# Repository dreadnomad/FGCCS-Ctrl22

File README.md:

# FGCCS-Ctrl22
Atmega4808-based charge controller for electric vehicles.
Inspired by SmartEVSE.

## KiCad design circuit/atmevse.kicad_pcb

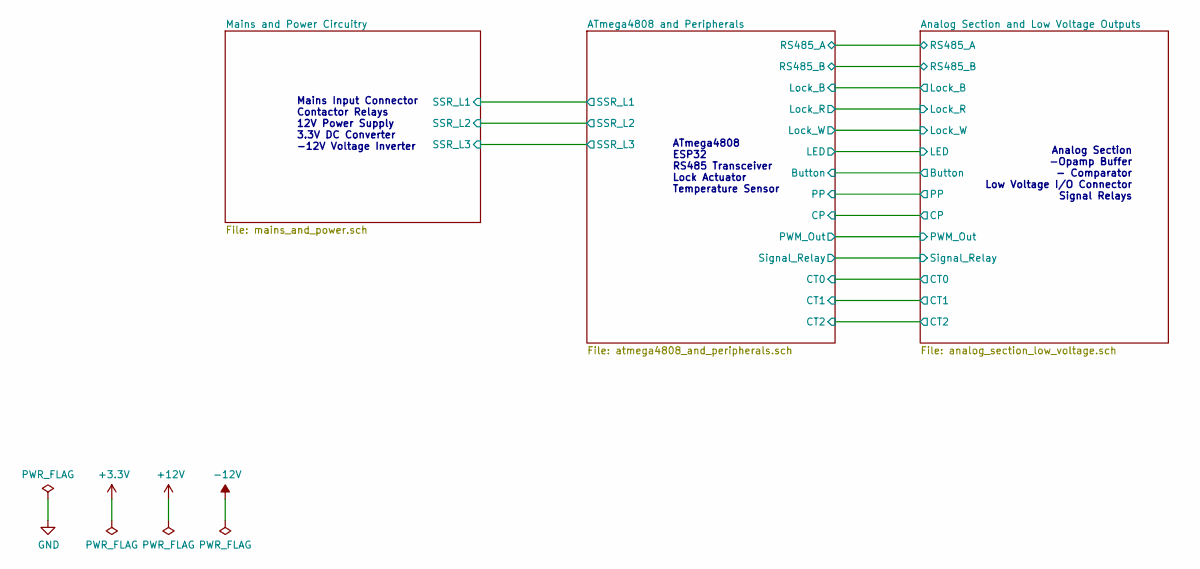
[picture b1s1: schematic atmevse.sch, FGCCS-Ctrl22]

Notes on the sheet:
Mains Input Connector Contactor Relays 12V Power Supply 3.3V DC Converter -12V Voltage Inverter
ATmega4808 ESP32 RS485 Transceiver Lock Actuator Temperature Sensor
Analog Section -Opamp Buffer - Comparator Low Voltage I/O Connector Signal Relays

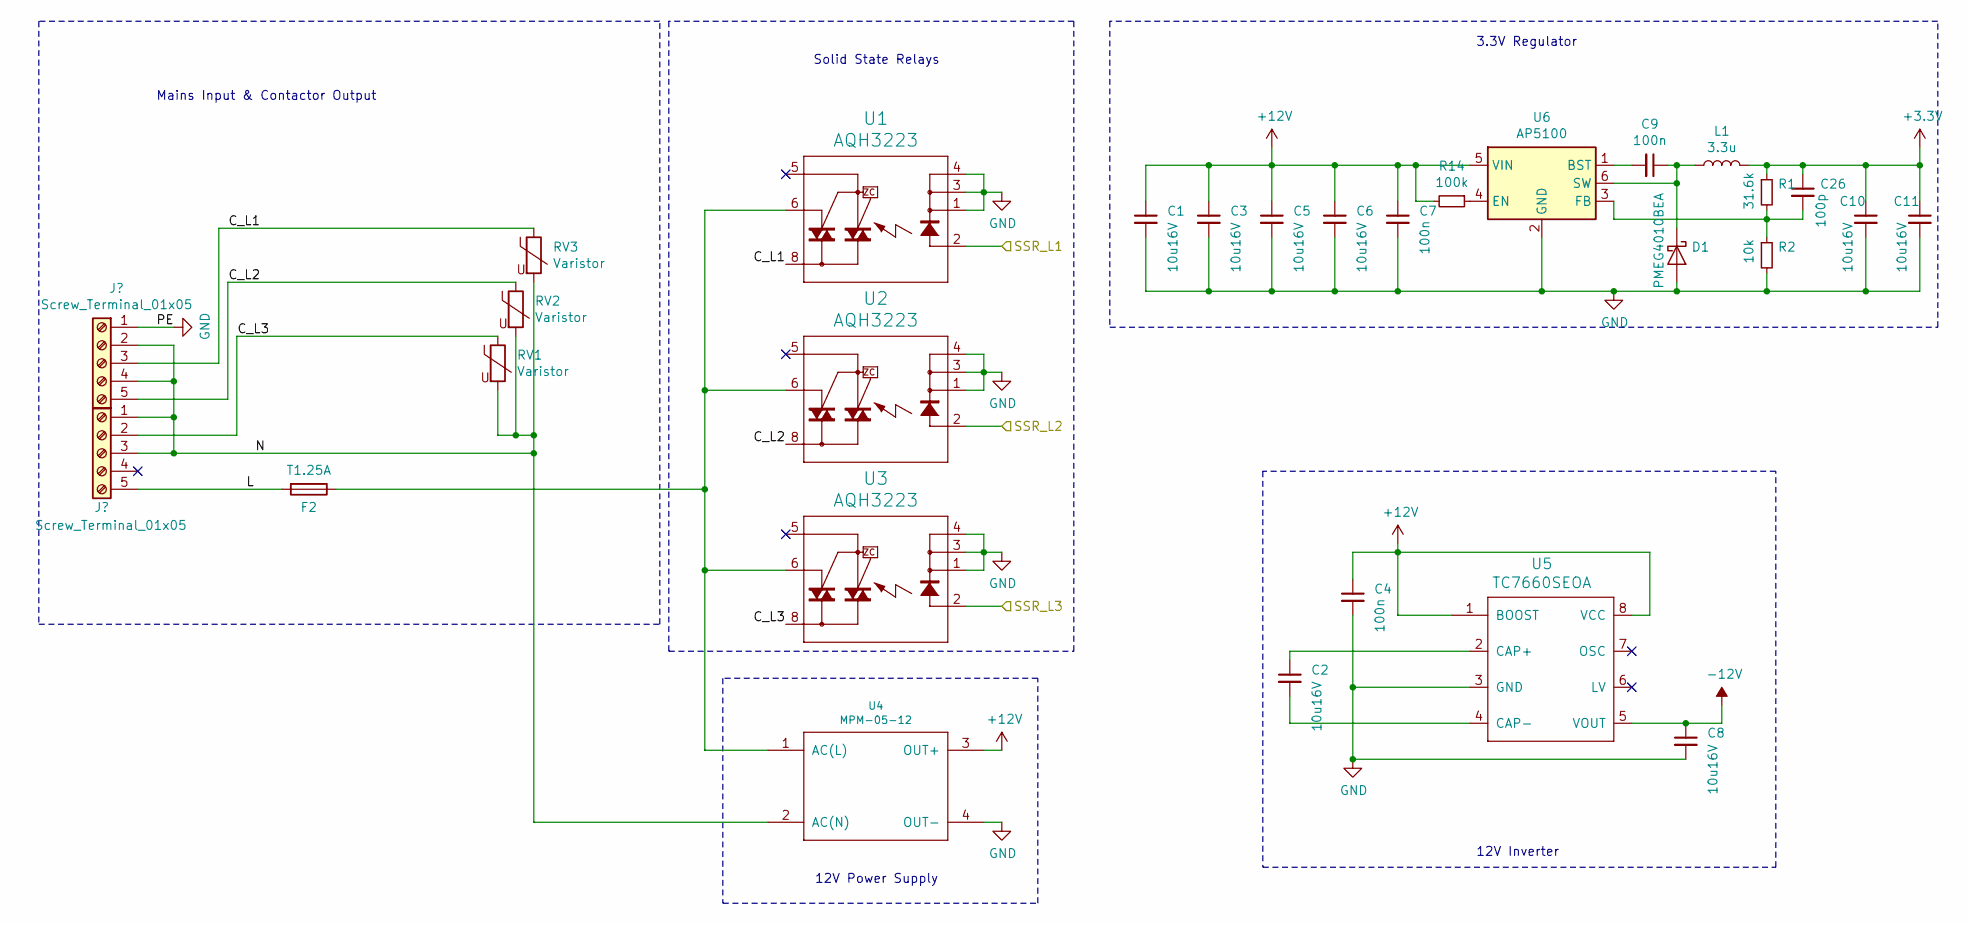
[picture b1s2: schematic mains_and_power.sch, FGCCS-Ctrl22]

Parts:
C1, C2, C3, C5, C6, C8, C10, C11: 10u16V; C_0805_2012Metric_Pad1.15x1.40mm_HandSolder; PartNo 963-EMK212ABJ106MG-T
C4, C7, C9: 100n; C_0805_2012Metric_Pad1.15x1.40mm_HandSolder; PartNo 963-EMF212B7104KGHT
C26: 100p; C_0805_2012Metric_Pad1.15x1.40mm_HandSolder; PartNo 77-VJ0805Y101KXACBC
D1: PMEG4010BEA; D_SOD-323_HandSoldering; PartNo 771-PMEG4010BEA,135
F2: T1.25A; TE5; PartNo 576-3921125000
L1: 3.3u; L_1210_3225Metric_Pad1.42x2.65mm_HandSolder; PartNo 810-MLF1608A3R3J
R1: 31.6k; R_0603_1608Metric_Pad1.05x0.95mm_HandSolder; PartNo 594-MCT06030C3162FP5
R2: 10k; R_0603_1608Metric_Pad1.05x0.95mm_HandSolder; PartNo 594-MCT06030C1002FP5
R14: 100k; R_0603_1608Metric_Pad1.05x0.95mm_HandSolder; PartNo 594-MCT06030C1003FP5
RV1, RV2, RV3: Varistor; RV_Disc_D15.5mm_W5mm_P7.5mm; PartNo 871-B72214S0271K551
U1, U2, U3: AQH3223; DIL07SMD; PartNo 769-AQH1213AX
U4: MPM-05-12; Converter_ACDC_MeanWell_IRM-10-xx_THT; PartNo 709-IRM10-12
U5: TC7660SEOA; SOIC-8_3.9x4.9mm_P1.27mm; PartNo 579-TC7660SEOA
U6: AP5100; SOT-23-6; PartNo 621-AP5100WG-7

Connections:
+3V3: C10.1, C11.1, C26.1, L1.2, R1.1; also elsewhere on the board
-12V: C8.1, U5.5 (VOUT); also elsewhere on the board
/ATmega4808 and Peripherals/SSR_L1: U1.2 (A); also elsewhere on the board
/ATmega4808 and Peripherals/SSR_L2: U2.2 (A); also elsewhere on the board
/ATmega4808 and Peripherals/SSR_L3: U3.2 (A); also elsewhere on the board
/Mains and Power Circuitry/C_L1: RV3.1, U1.8 (DS1); also elsewhere on the board
/Mains and Power Circuitry/C_L2: RV2.1, U2.8 (DS1); also elsewhere on the board
/Mains and Power Circuitry/C_L3: RV1.1, U3.8 (DS1); also elsewhere on the board
/Mains and Power Circuitry/L: F2.2; also elsewhere on the board
unnamed: C2.1, U5.2 (CAP+)
unnamed: C2.2, U5.4 (CAP-)
unnamed: C9.1, D1.1 (K), L1.1, U6.6 (SW)
unnamed: C9.2, U6.1 (BST)
unnamed: C26.2, R1.2, R2.1, U6.3 (FB)
unnamed: R14.1, U6.4 (EN)

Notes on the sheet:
Solid State Relays
Mains Input & Contactor Output
12V Power Supply
3.3V Regulator
12V Inverter

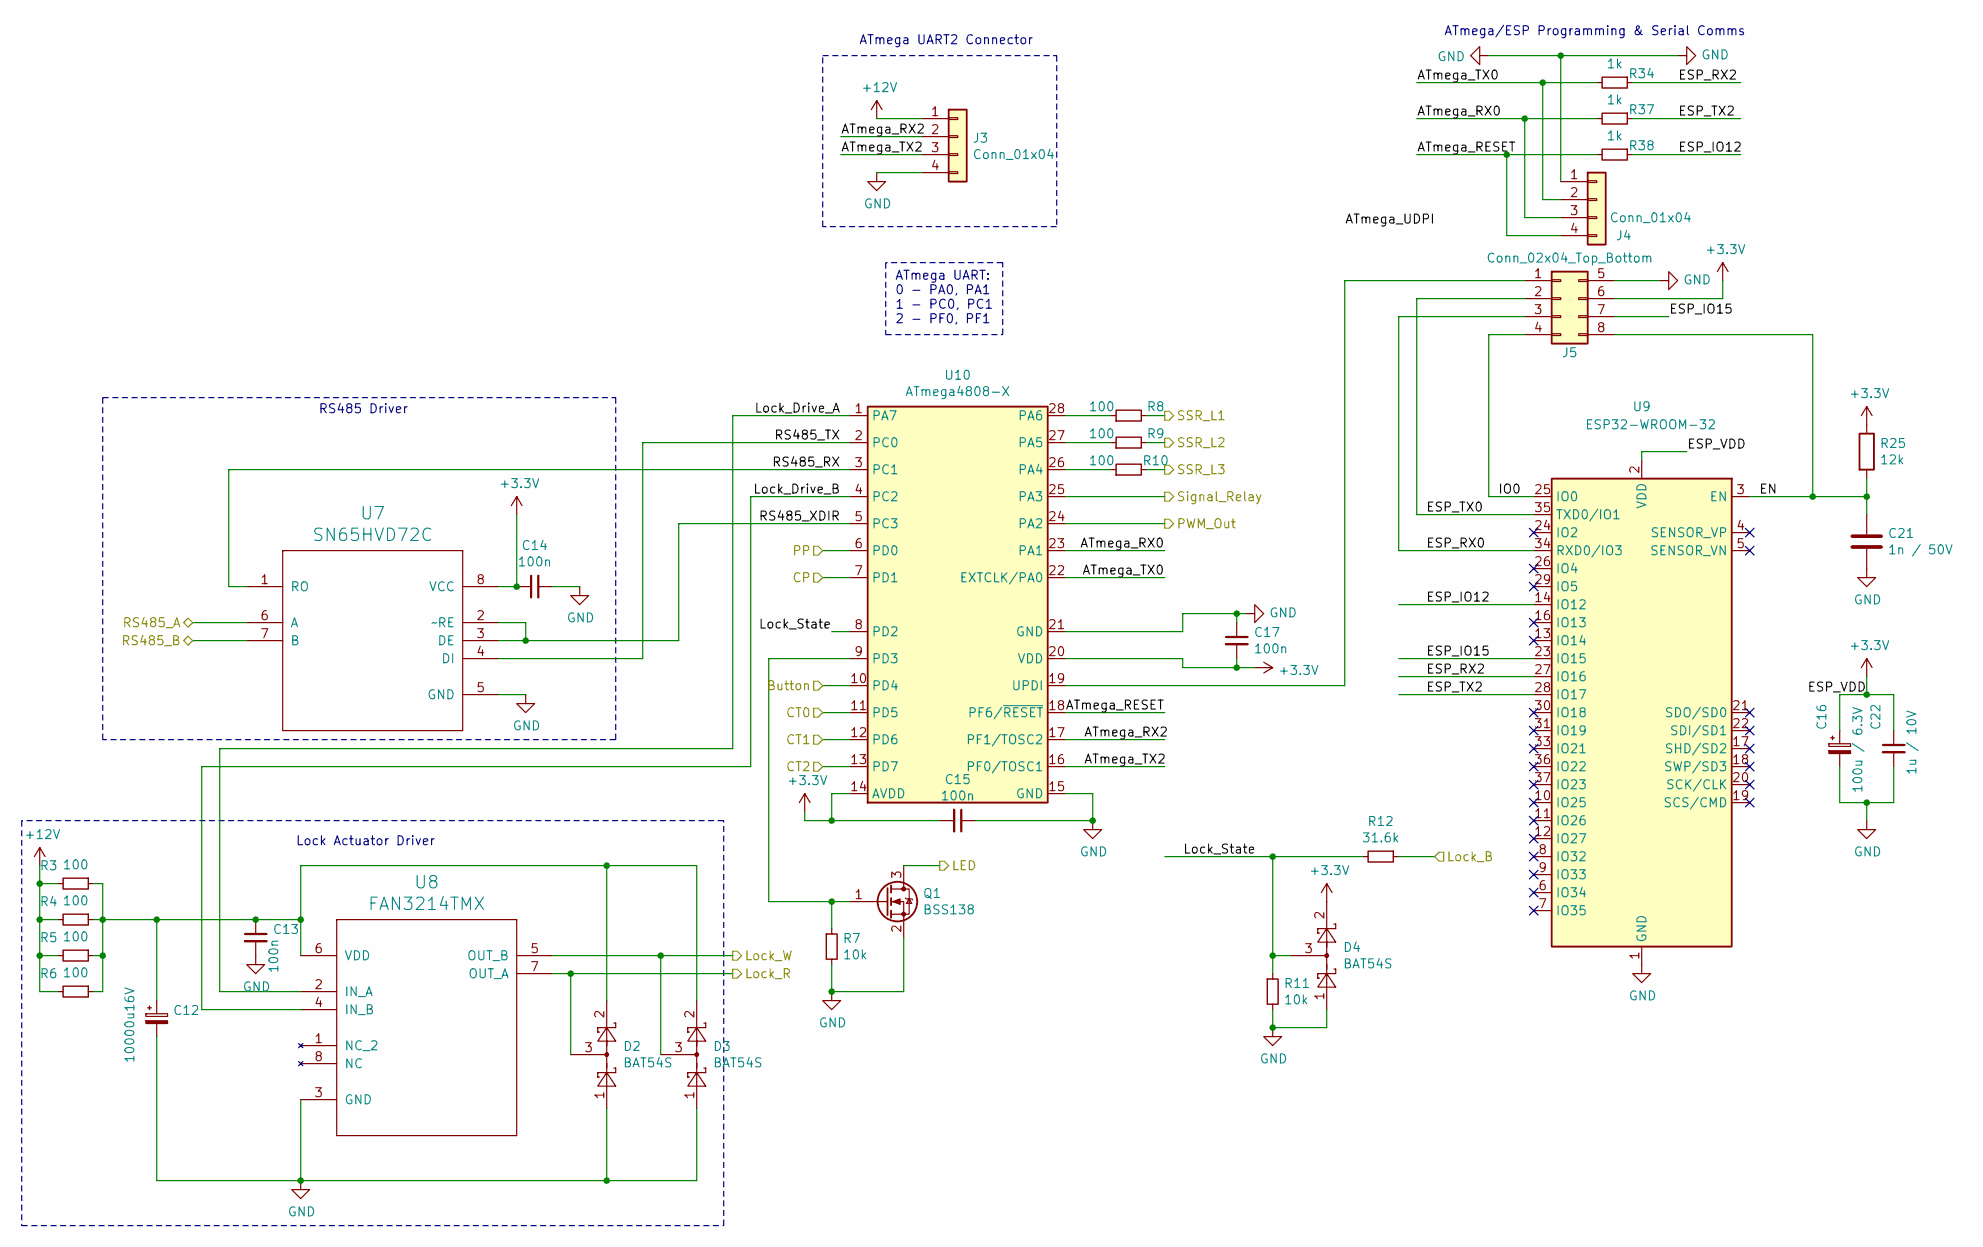
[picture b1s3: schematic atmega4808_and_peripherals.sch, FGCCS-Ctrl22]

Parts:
C12: 10000u16V; CP_Radial_D22.0mm_P10.00mm_SnapIn; PartNo 871-B41231A4109M000
C13, C14, C15, C17: 100n; C_0805_2012Metric_Pad1.15x1.40mm_HandSolder; PartNo 963-EMF212B7104KGHT
C16: 100u / 6.3V; CP_EIA-2012-15_AVX-P_Pad1.30x1.05mm_HandSolder; PartNo 581-TLCR107M006RTA
C21: 1n / 50V; C_0805_2012Metric_Pad1.15x1.40mm_HandSolder; PartNo 77-VJ0805A102KXAAC
C22: 1u / 10V; C_0805_2012Metric_Pad1.15x1.40mm_HandSolder; PartNo 77-VJ805Y105KXARW1BC
D2, D3, D4: BAT54S; SOT-23_Handsoldering; PartNo 583-BAT54S
J3: Conn_01x04; UART2-Header; PartNo 710-61304011121
J4: Conn_01x04; UART0-Header
J5: Conn_02x04_Top_Bottom; PROGRAM-Header; PartNo 710-61300821121
Q1: BSS138; SOT-23_Handsoldering; PartNo 512-BSS138
R3, R4, R5, R6, R8, R9, R10: 100; R_0603_1608Metric_Pad1.05x0.95mm_HandSolder; PartNo 594-MCT06030C1000FP5
R7, R11: 10k; R_0603_1608Metric_Pad1.05x0.95mm_HandSolder; PartNo 594-MCT06030C1002FP5
R12: 31.6k; R_0603_1608Metric_Pad1.05x0.95mm_HandSolder; PartNo 594-MCT06030C3162FP5
R25: 12k; R_0603_1608Metric_Pad1.05x0.95mm_HandSolder; PartNo 594-MCT06030C1202FP5
R34, R37, R38: 1k; R_0603_1608Metric_Pad1.05x0.95mm_HandSolder
U7: SN65HVD72C; SOIC-8_3.9x4.9mm_P1.27mm; PartNo 595-SN65HVD72D
U8: FAN3214TMX; SOIC-8_3.9x4.9mm_P1.27mm; PartNo 512-FAN3214TMX
U9: ESP32-WROOM-32
U10: ATmega4808-X; SSOP-28_5.3x10.2mm_P0.65mm

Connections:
+3V3: C14.1, C15.2, C16.1, C17.2, C22.1, D4.2, J5.6, R25.1, U7.8 (VCC), U9.2 (VDD), U10.14 (AVDD), U10.20 (VDD); also elsewhere on the board
/ATmega4808 and Peripherals/ATmega_RESET: J4.4, R38.2, U10.18 (PF6/~RESET)
/ATmega4808 and Peripherals/ATmega_RX0: J4.3, R37.2, U10.23 (PA1)
/ATmega4808 and Peripherals/ATmega_RX2: J3.2, U10.17 (PF1/TOSC2)
/ATmega4808 and Peripherals/ATmega_TX0: J4.2, R34.2, U10.22 (EXTCLK/PA0)
/ATmega4808 and Peripherals/ATmega_TX2: J3.3, U10.16 (PF0/TOSC1)
/ATmega4808 and Peripherals/Button: U10.10 (PD4); also elsewhere on the board
/ATmega4808 and Peripherals/CP: U10.7 (PD1); also elsewhere on the board
/ATmega4808 and Peripherals/CT0: U10.11 (PD5); also elsewhere on the board
/ATmega4808 and Peripherals/CT1: U10.12 (PD6); also elsewhere on the board
/ATmega4808 and Peripherals/CT2: U10.13 (PD7); also elsewhere on the board
/ATmega4808 and Peripherals/EN: C21.1, J5.8, R25.2, U9.3 (EN)
/ATmega4808 and Peripherals/ESP_IO12: R38.1, U9.14 (IO12)
/ATmega4808 and Peripherals/ESP_IO15: J5.7, U9.23 (IO15)
/ATmega4808 and Peripherals/ESP_RX0: J5.3, U9.34 (RXD0/IO3)
/ATmega4808 and Peripherals/ESP_RX2: R34.1, U9.27 (IO16)
/ATmega4808 and Peripherals/ESP_TX0: J5.2, U9.35 (TXD0/IO1)
/ATmega4808 and Peripherals/ESP_TX2: R37.1, U9.28 (IO17)
/ATmega4808 and Peripherals/IO0: J5.4, U9.25 (IO0)
/ATmega4808 and Peripherals/LED: Q1.3 (D); also elsewhere on the board
/ATmega4808 and Peripherals/Lock_B: R12.1; also elsewhere on the board
/ATmega4808 and Peripherals/Lock_Drive_A: U8.2 (IN_A), U10.1 (PA7)
/ATmega4808 and Peripherals/Lock_Drive_B: U8.4 (IN_B), U10.4 (PC2)
/ATmega4808 and Peripherals/Lock_R: D2.3, U8.7 (OUT_A); also elsewhere on the board
/ATmega4808 and Peripherals/Lock_State: D4.3, R11.1, R12.2, U10.8 (PD2)
/ATmega4808 and Peripherals/Lock_W: D3.3, U8.5 (OUT_B); also elsewhere on the board
/ATmega4808 and Peripherals/PP: U10.6 (PD0); also elsewhere on the board
/ATmega4808 and Peripherals/PWM_Out: U10.24 (PA2); also elsewhere on the board
/ATmega4808 and Peripherals/RS485_A: U7.6 (A); also elsewhere on the board
/ATmega4808 and Peripherals/RS485_B: U7.7 (B); also elsewhere on the board
/ATmega4808 and Peripherals/RS485_RX: U7.1 (RO), U10.3 (PC1)
/ATmega4808 and Peripherals/RS485_TX: U7.4 (DI), U10.2 (PC0)
/ATmega4808 and Peripherals/RS485_XDIR: U7.2 (~~RE), U7.3 (DE), U10.5 (PC3)
/ATmega4808 and Peripherals/SSR_L1: R8.2; also elsewhere on the board
/ATmega4808 and Peripherals/SSR_L2: R9.2; also elsewhere on the board
/ATmega4808 and Peripherals/SSR_L3: R10.2; also elsewhere on the board
/ATmega4808 and Peripherals/Signal_Relay: U10.25 (PA3); also elsewhere on the board
unnamed: C12.1, C13.1, D2.2, D3.2, R3.1, R4.1, R5.1, R6.1, U8.6 (VDD)
unnamed: J5.1, U10.19 (UPDI)
unnamed: Q1.1 (G), R7.1, U10.9 (PD3)
unnamed: R8.1, U10.28 (PA6)
unnamed: R9.1, U10.27 (PA5)
unnamed: R10.1, U10.26 (PA4)

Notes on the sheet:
RS485 Driver
Lock Actuator Driver
ATmega/ESP Programming & Serial Comms
ATmega UART: 0 - PA0, PA1 1 - PC0, PC1 2 - PF0, PF1
ATmega UART2 Connector

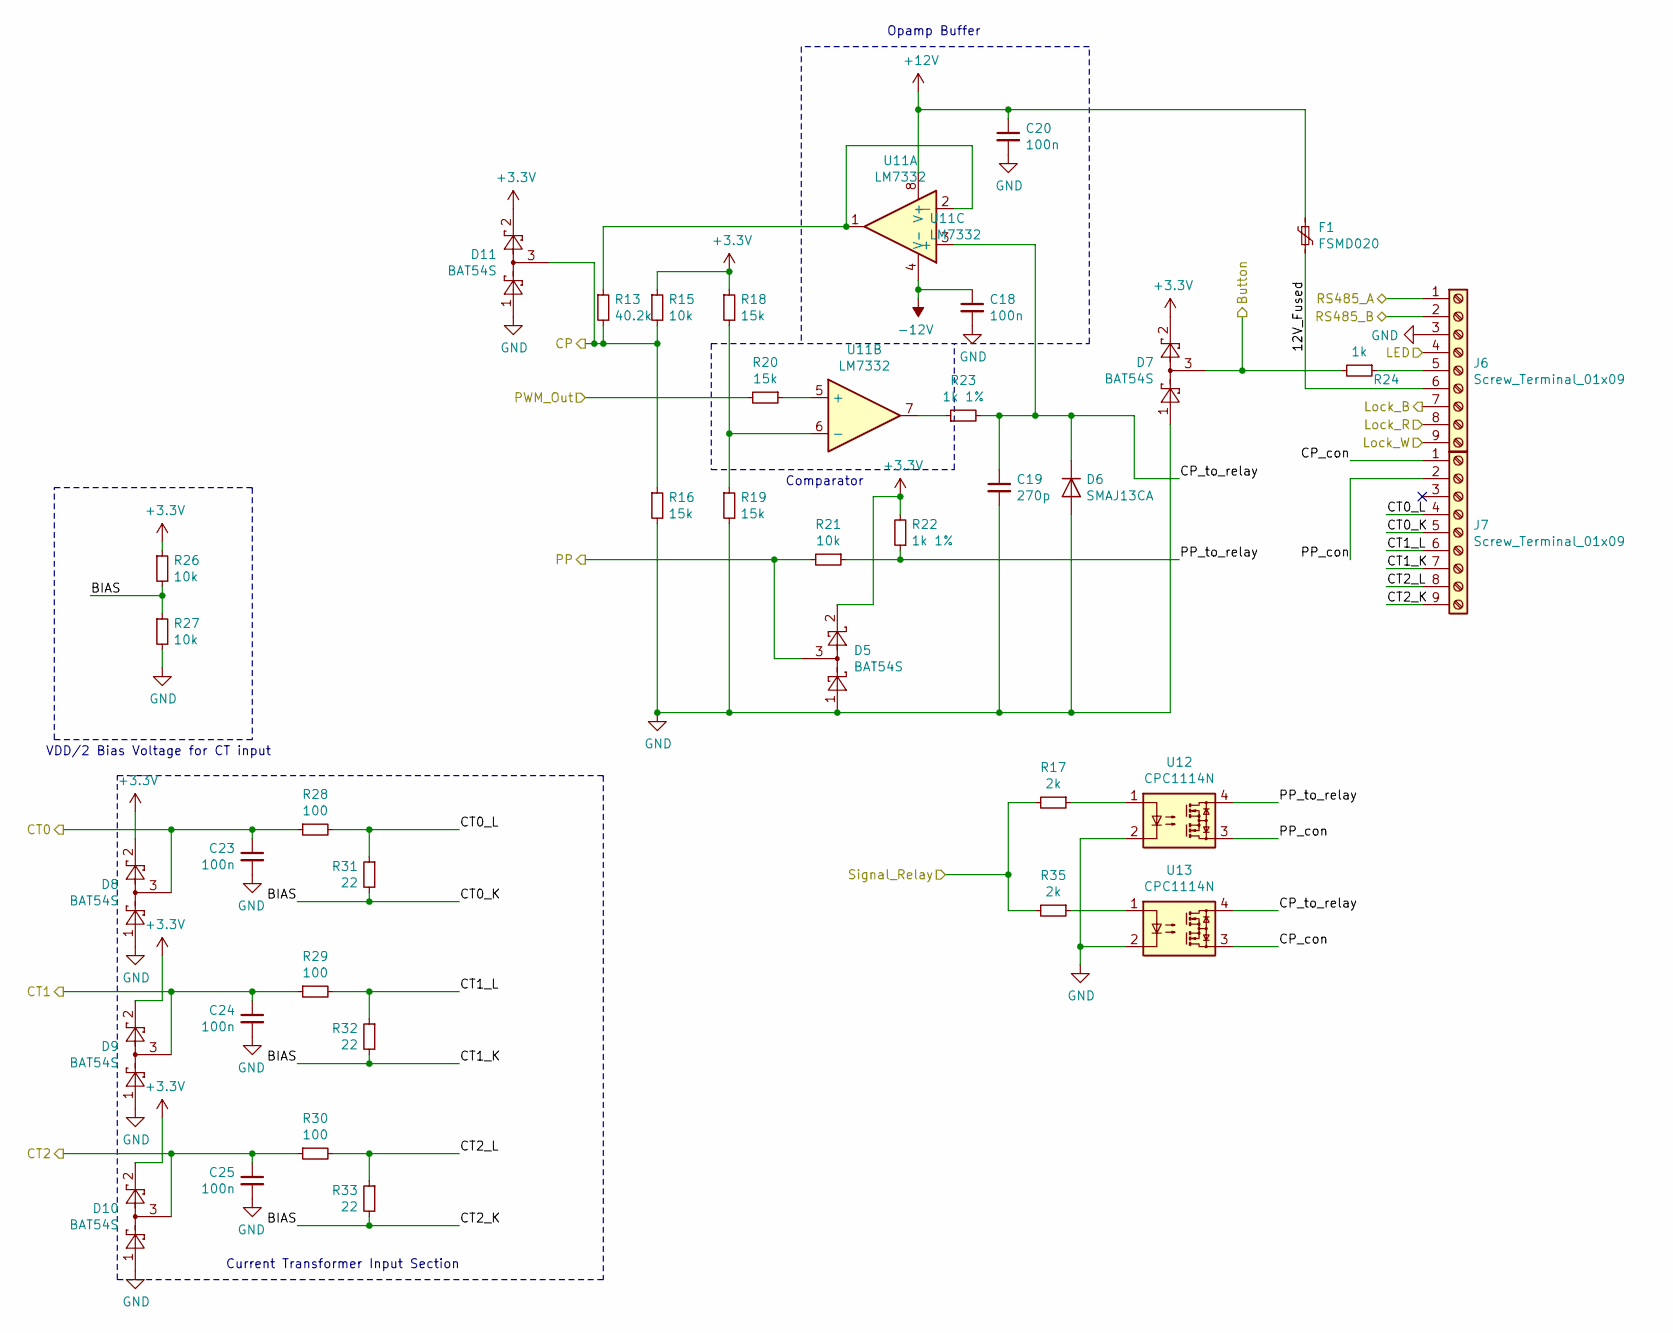
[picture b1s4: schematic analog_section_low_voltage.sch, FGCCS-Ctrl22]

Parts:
C18, C20, C23, C24, C25: 100n; C_0805_2012Metric_Pad1.15x1.40mm_HandSolder; PartNo 963-EMF212B7104KGHT
C19: 270p; C_0805_2012Metric_Pad1.15x1.40mm_HandSolder; PartNo 77-VJ0805A271KXJPBC
D5, D7: BAT54S; SOT-23_Handsoldering; PartNo 583-BAT54S
D6: SMAJ13CA; D_SMA_Handsoldering; PartNo 652-SMAJ13CA
D8, D9, D10, D11: BAT54S; SOT-23_Handsoldering
F1: FSMD020; Fuse_1812_4532Metric_Pad1.30x3.40mm_HandSolder; PartNo 576-1812L020PR
J6: Screw_Terminal_01x09; lv_screw_9pin_1
J7: Screw_Terminal_01x09; lv_screw_9pin_2
R13: 40.2k; R_0603_1608Metric_Pad1.05x0.95mm_HandSolder; PartNo 594-MCT06030C4022FP5
R15, R21, R26, R27: 10k; R_0603_1608Metric_Pad1.05x0.95mm_HandSolder; PartNo 594-MCT06030C1002FP5
R16, R18, R19, R20: 15k; R_0603_1608Metric_Pad1.05x0.95mm_HandSolder; PartNo 594-MCT06030C1502FP5
R17, R35: 2k; R_0603_1608Metric_Pad1.05x0.95mm_HandSolder; PartNo 594-MCT06030C2001FP5
R22, R23: 1k 1%; R_0603_1608Metric_Pad1.05x0.95mm_HandSolder; PartNo 594-MCT06030C1001FP5
R24: 1k; R_0603_1608Metric_Pad1.05x0.95mm_HandSolder; PartNo 594-MCT06030C1000FP5
R28, R29, R30: 100; R_0603_1608Metric_Pad1.05x0.95mm_HandSolder; PartNo 594-MCT06030C1000FP5
R31, R32, R33: 22; R_0603_1608Metric_Pad1.05x0.95mm_HandSolder; PartNo 594-MCT06030C2209FP5
U11: LM7332; SOIC-8_3.9x4.9mm_P1.27mm; PartNo 926-LM7332MA/NOPB
U12, U13: CPC1114N; SOP-4_3.8x4.1mm_P2.54mm; PartNo 849-CPC1114N

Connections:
+3V3: D5.2, D7.2, D8.2, D9.2, D10.2, D11.2, R15.1, R18.1, R22.2, R26.1; also elsewhere on the board
-12V: C18.1, U11.4 (V-); also elsewhere on the board
/ATmega4808 and Peripherals/Button: D7.3, R24.2; also elsewhere on the board
/ATmega4808 and Peripherals/CP: D11.3, R13.2, R15.2, R16.1; also elsewhere on the board
/ATmega4808 and Peripherals/CT0: C23.1, D8.3, R28.1; also elsewhere on the board
/ATmega4808 and Peripherals/CT1: C24.1, D9.3, R29.1; also elsewhere on the board
/ATmega4808 and Peripherals/CT2: C25.1, D10.3, R30.1; also elsewhere on the board
/ATmega4808 and Peripherals/LED: J6.4; also elsewhere on the board
/ATmega4808 and Peripherals/Lock_B: J6.7; also elsewhere on the board
/ATmega4808 and Peripherals/Lock_R: J6.8; also elsewhere on the board
/ATmega4808 and Peripherals/Lock_W: J6.9; also elsewhere on the board
/ATmega4808 and Peripherals/PP: D5.3, R21.2; also elsewhere on the board
/ATmega4808 and Peripherals/PWM_Out: R20.2; also elsewhere on the board
/ATmega4808 and Peripherals/RS485_A: J6.1; also elsewhere on the board
/ATmega4808 and Peripherals/RS485_B: J6.2; also elsewhere on the board
/ATmega4808 and Peripherals/Signal_Relay: R17.2, R35.2; also elsewhere on the board
/Analog Section and Low Voltage Outputs/12V_Fused: F1.2, J6.6
/Analog Section and Low Voltage Outputs/BIAS: J7.5, J7.7, J7.9, R26.2, R27.1, R31.2, R32.2, R33.2
/Analog Section and Low Voltage Outputs/CP_con: J7.1, U13.3
/Analog Section and Low Voltage Outputs/CP_to_relay: C19.1, D6.1 (K), R23.2, U11.3 (+), U13.4
/Analog Section and Low Voltage Outputs/CT0_L: J7.4, R28.2, R31.1
/Analog Section and Low Voltage Outputs/CT1_L: J7.6, R29.2, R32.1
/Analog Section and Low Voltage Outputs/CT2_L: J7.8, R30.2, R33.1
/Analog Section and Low Voltage Outputs/PP_con: J7.2, U12.3
/Analog Section and Low Voltage Outputs/PP_to_relay: R21.1, R22.1, U12.4
unnamed: J6.5, R24.1
unnamed: R13.1, U11.1, U11.2 (-)
unnamed: R17.1, U12.1
unnamed: R18.2, R19.1, U11.6 (-)
unnamed: R20.1, U11.5 (+)
unnamed: R23.1, U11.7
unnamed: R35.1, U13.1

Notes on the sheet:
Opamp Buffer
Comparator
Current Transformer Input Section
VDD/2 Bias Voltage for CT input

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
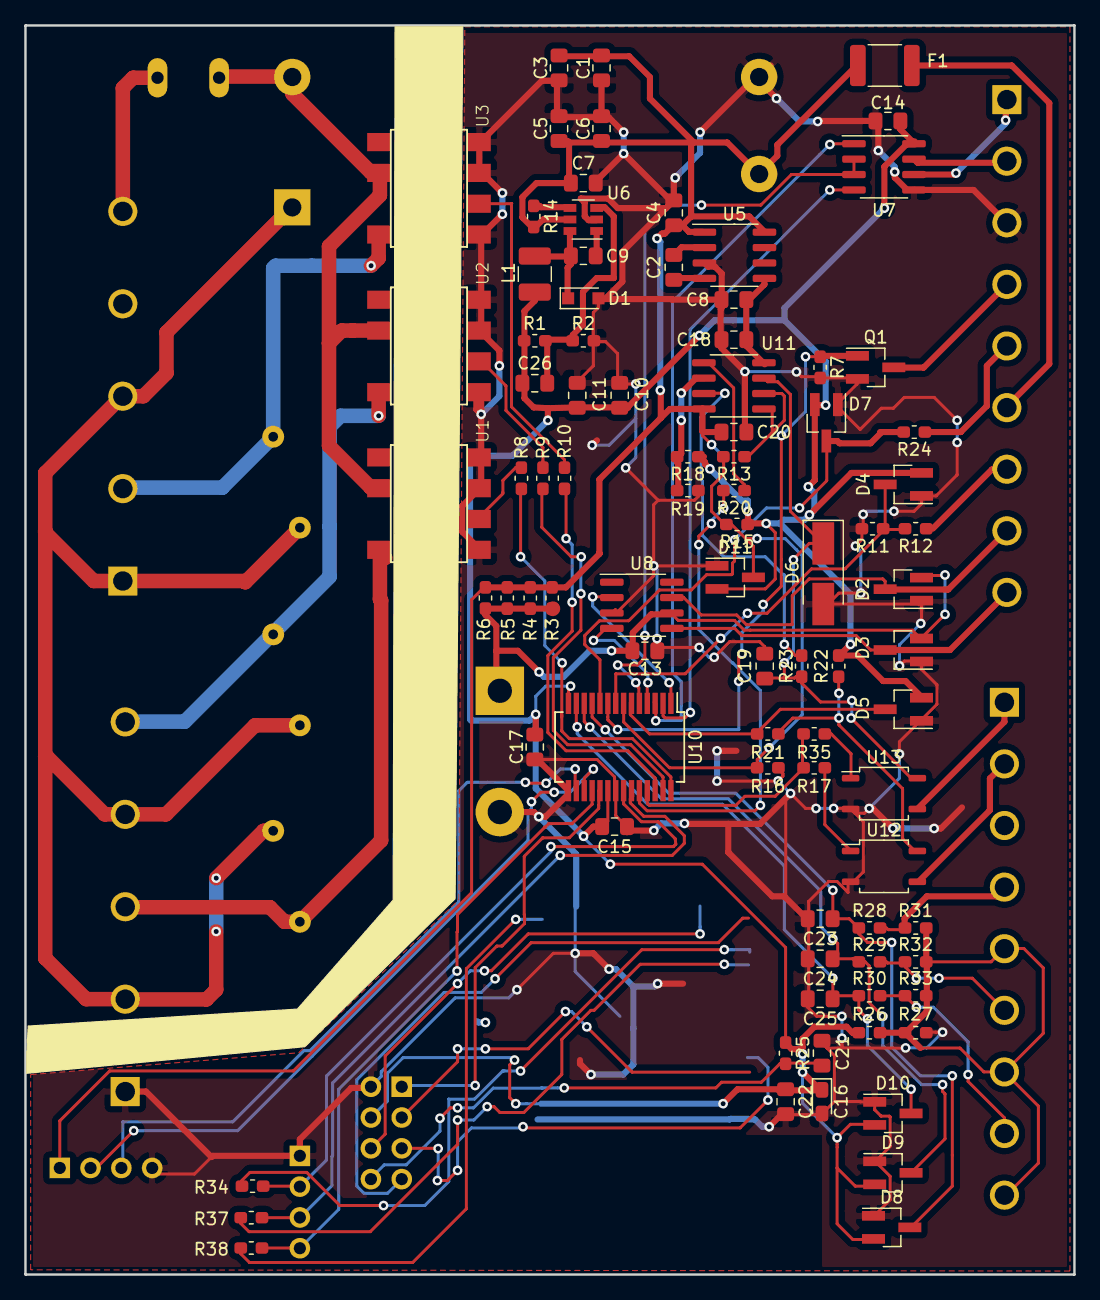
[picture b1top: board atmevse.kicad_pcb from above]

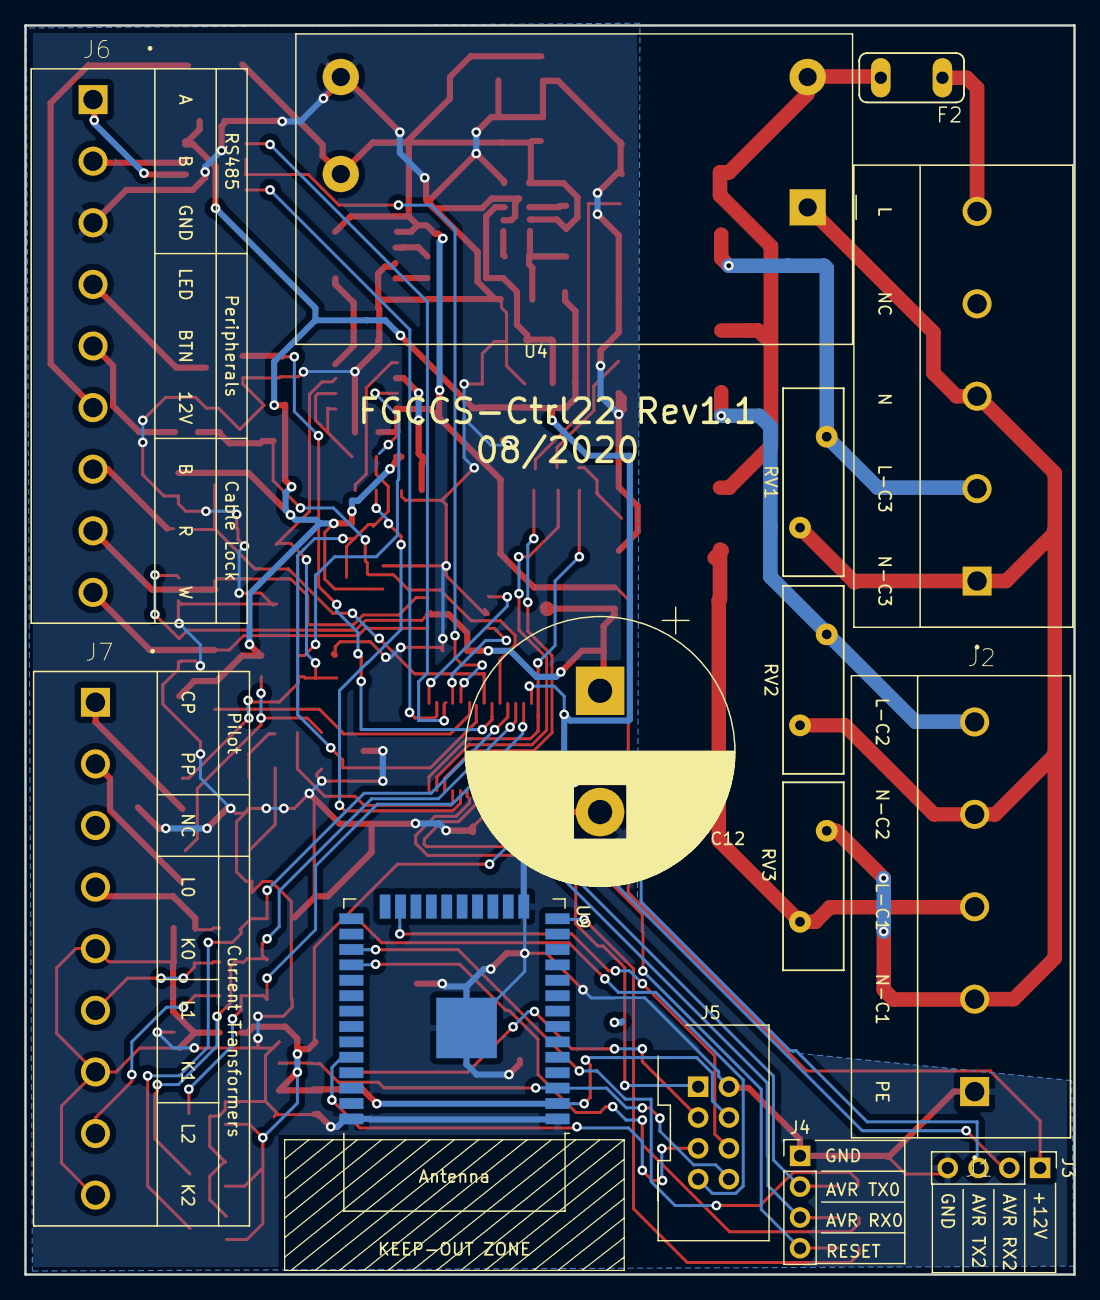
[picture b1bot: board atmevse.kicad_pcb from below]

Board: 2 copper layers, 86.5 x 103.0 mm, 101 parts (14 on the bottom side), 74 nets.

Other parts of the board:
J1: Screw_Terminal_01x05; hv_screw_5pin_1
J2: Screw_Terminal_01x05; hv_screw_5pin_2

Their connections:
/Mains and Power Circuitry/C_L1: J1.3; also elsewhere on the board
/Mains and Power Circuitry/C_L2: J1.5; also elsewhere on the board
/Mains and Power Circuitry/C_L3: J2.2; also elsewhere on the board
/Mains and Power Circuitry/L: J2.5; also elsewhere on the board

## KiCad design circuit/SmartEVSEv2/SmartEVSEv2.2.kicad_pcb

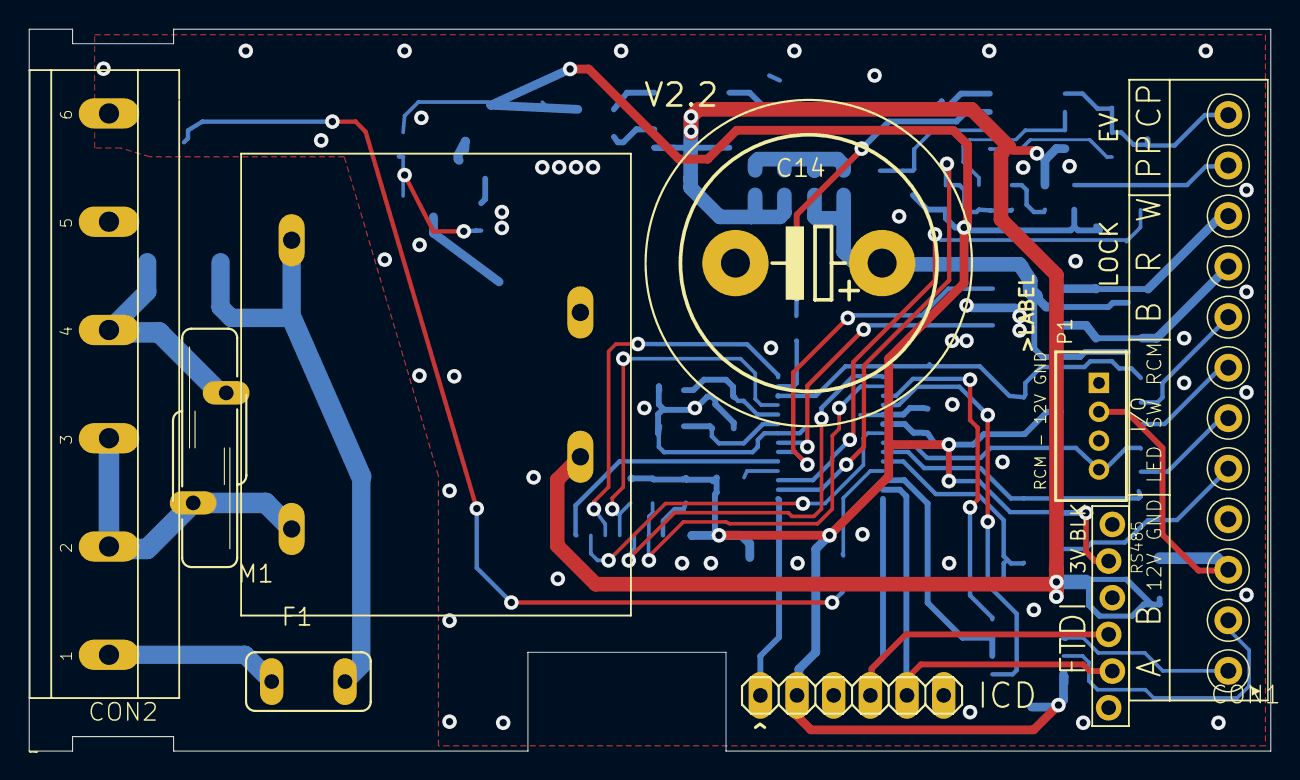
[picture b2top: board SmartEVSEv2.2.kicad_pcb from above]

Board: 2 copper layers, 86.0 x 50.0 mm, 77 parts (0 on the bottom side), 56 nets.

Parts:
C1, C2: 18p; C0603
C3, C7, C9, C12, C15, C16, C18, C20, C22: 10u16v; C0805
C4, C5, C8, C10, C11, C13, C17, C19, C21: 100n; C0603
C6: 270p; C0805
C14: 10000u 16V; EB22,5D
CON1: 3.5MM_12PIN; 12PIN
CON2: DG128-7.5; P_AST027-06
CON3: JST_10PIN_FFC
D1: SMAJ13CA; DO214AC
D2, D3, D4, D5, D8, D9: BAT54S; SOT23
D6: PMEG4010CEH; SOD-123FL
F1: T1.25A; TE5
F2: 0.2A Polyfuse; R1210
FTDI1: FTDI; 1X06-BIGLOCK
IC1: AOZ1280CI; SOT23-6
IC2: LM7332MA; SO08
IC3: MCP9700A; SOT23
IC4: PIC18F26K22-I/SOSSOP; SOP65P780X200-28N
IC5: SN65HVD72; SOIC127P600X175-8N
IC6: FAN3214TMX; SOIC127P600X175-8N
IC7: TC7660S; SO08
ICD1: ICD; 1X06
K1: AQH1213AX; DIL07SMD
L1: 2.2uH; MCSD43
M1: V275LA20AP; S14K40
P1: B4B-PH-K
Q1: CTS_32X25_SMD; CTS_32X25
R1, R17: 31K6; R0603
R2, R3, R4, R22, R23: 15K; R0603
R5: 10k; R0603
R6: 15k; R0603
R7, R12: 1K 1%; R0603
R8: 40k2; R0603
R9, R11, R13, R16: 10K; R0603
R10, R14, R15, R18, R19, R20, R21: 100R; R0603
T1: BSS138; SOT23
U$1, U$3, U$4: FIDUCIAL; FIDUCIAL_1MM
U$2: VTX-214-005-112

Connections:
+12V: C8.1, C16.1, C17.1, C18.1, C20.1, C21.1, C22.1, F2.2, IC1.4, IC1.5, IC2.8, IC7.1, IC7.8, R20.1, R21.1, U$2.3
-12V: C12.1, C19.1, IC2.4, IC7.5
/12V_FUSED: CON1.3, F2.1, P1.2
/B1: CON3.3, IC4.21
/IO1: IC4.24, R13.2, T1.1
/IO2: D8.3, IC4.23, R15.1
/IO3: D9.3, IC4.22, P1.4, R18.1
/LCD_A0_B2: CON3.5, IC4.11, R22.1
/LCD_CLK: CON3.4, IC4.14
/LCD_LED: CON3.2, IC4.5
/LCD_RST: CON3.6, IC4.15
/LCD_SDO_B3: CON3.7, IC4.16, R23.1
/LED_12V: CON1.5, T1.3
/RS485_A: CON1.1, IC5.6
/RS485_B: CON1.2, IC5.7
/RX: FTDI1.3, IC4.28, ICD1.4
/TX: FTDI1.2, IC4.27, ICD1.5
GND: C1.2, C2.2, C3.2, C5.2, C6.2, C7.1, C8.2, C10.2, C11.2, C12.2, C13.2, C14.-, C15.1, C16.2, C17.2, C18.2, C19.2, C20.2, C21.2, C22.2, CON1.4, CON2.P$6, CON3.8, D1.A, D2.1, D3.1, D4.1, D5.1, D6.A, D8.1, D9.1, FTDI1.6, IC1.2, IC3.3, IC4.8, IC4.19, IC5.5, IC6.3, IC7.3, ICD1.3, K1.1, K1.3, K1.4, P1.1, Q1.2, Q1.4, R4.2, R6.2, R9.2, R13.1, R16.1, T1.2, U$2.4
unnamed: C1.1, IC4.10, Q1.3
unnamed: C2.1, IC4.9, Q1.1
unnamed: C4.1, IC1.1
unnamed: C4.2, D6.C, IC1.6, L1.2
unnamed: C6.1, CON1.12, D1.C, IC2.5, R7.2
unnamed: C9.1, IC7.2
unnamed: C9.2, IC7.4
unnamed: C13.1, C14.+, D4.2, D5.2, IC6.6, R14.2, R19.2
unnamed: CON1.6, R15.2
unnamed: CON1.7, R18.2
unnamed: CON1.8, R1.2
unnamed: CON1.9, D4.3, IC6.7
unnamed: CON1.10, D5.3, IC6.5
unnamed: CON1.11, R11.2, R12.2
unnamed: CON2.P$1, F1.2
unnamed: CON2.P$2, CON2.P$3, M1.1, U$2.2
unnamed: CON2.P$4, K1.8, M1.2
unnamed: D2.3, IC4.3, R11.1
unnamed: D3.3, IC4.12, R1.1, R16.2
unnamed: F1.1, K1.6, U$2.1
unnamed: IC1.3, R9.1, R17.2
unnamed: IC2.1, R7.1
unnamed: IC2.2, R3.2, R4.1
unnamed: IC2.3, R2.2
unnamed: IC2.6, IC2.7, R8.1
unnamed: IC3.2, IC4.4
unnamed: IC4.1, ICD1.1
unnamed: IC4.2, R5.2, R6.1, R8.2
unnamed: IC4.6, IC6.4
unnamed: IC4.7, IC6.2
unnamed: IC4.13, R2.1
unnamed: IC4.17, IC5.4
unnamed: IC4.18, IC5.1
unnamed: IC4.25, R10.2
unnamed: IC4.26, IC5.2, IC5.3
unnamed: K1.2, R10.1
unnamed: R14.1, R19.1, R20.2, R21.2
VCC: C3.1, C5.1, C7.2, C10.1, C11.1, C15.2, CON3.10, D2.2, D3.2, D8.2, D9.2, FTDI1.5, IC3.1, IC4.20, IC5.8, ICD1.2, L1.1, R3.1, R5.1, R12.1, R17.1, R22.2, R23.2

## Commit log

2020-04-01 Collect datasheets for circuit design
2020-04-01 Collect information on circuit
    Note circuit functionality and pin config in SmartEVSE circuit diagram.
    This determines ATmega4808 config and aids in understanding the existing
    circuit components.
2020-04-01 Add TODO document
2020-04-03 Add ESP32 datasheet
2020-04-03 Add pin config tables to REVENG.md
2020-04-03 Complete SmartEVSE circuit analysis and update TODO
2020-04-06 Update REVENG.md with pin directions
2020-04-07 Import SmartEVSE schematic and layout into Kicad
2020-04-07 Add ATmega pin config v1
2020-04-08 Remove SmartEvse kicad project from repo
2020-04-08 Add initial kicad project for atmevse
2020-04-08 Add imported Symbol library from SmartEVSEv2
2020-04-08 Add imported footprints from SmartEVSE project
2020-04-08 Clean up the symbol library
2020-04-08 Capture mains and power supply schematics of atmevse_v1
2020-04-09 Change folder and project structure of kicad circuit data
2020-04-09 Continue schematic capture
2020-04-10 Update to rev0.1 of atmevse circuit
2020-04-10 remove qucs sim files
2020-05-12 Update Schematic with Prof. Moor's suggestions
2020-05-13 Add CT input simulation files
2020-05-13 Update schematic with suggestions
2020-05-14 Edit schematic
    Moved CT input to J2
2020-05-14 Add simulation for 12V button circuit
2020-05-18 Update pin configuration
    All pins used now, PF0 & PF1 used for UART2
2020-05-18 Add simulation files for button w/o voltage divider
    Second simulation added for button input, which topology is better remains to be seen
2020-05-18 Update button simulation
2020-05-18 Edit schematic to rev0.6
    Updated schematic with ESP32, CT inputs moved, Button input circuit new.
    Temp sens removed, will use internal sensor in ATmega4808
2020-05-18 First ATmega test program
    ATmega4808 & Atmel ICE UDPI programmer tested with LED-blinking program
2020-05-18 Update TODO list
2020-05-20 Update schematic
    Schematic updated with latest changes and preparation for footprint assignment
2020-05-20 Add kdev project for linux development
2020-05-21 Change project name to blink_test
2020-05-21 Add uart_test project
2020-05-28 Add new component data in schematic
    Updated components and footprints in schematic
2020-05-29 Update Parts List with Mouser ordering info
2020-06-01 Finish schematic rev1 and footprint assignment
2020-06-03 Update first layout draft
2020-06-10 Finish Rev1 PCB Layout and send off to fab
    PCB layout is done now, collect Revisions in REVISION.md
    TODO updated with current tasks
2020-06-15 Build optiboot for atmega4808
2020-06-23 Add arduino sketches and optiboot elf
    Arduino sketches for testing serial protocol
    Optiboot ELF for 4808 working
2020-06-30 Update revision list in REVISION.md
    first draft of ToC for documentation
2020-07-01 Add new version of bootloader ELF and HEXxy
2020-07-01 Update Bootloader
2020-07-07 Add compiled sketch bins
2020-07-07 Add avrdude command for sketch upload
2020-07-07 New avrdude upload cmd
2020-07-07 Debugging avrdude /w optiboot
2020-07-07 Update upload script
2020-07-07 Working on AVRDUDE troubleshooting
2020-07-07 Edit avrdude upload script
2020-07-20 Firmware initial commit
2020-07-20 Implement basic command interpreter
    Command interpreter in cmd.h/cmd.c can execute registered functions via serial input
2020-07-20 Implement system commands and parameter table
2020-07-20 Implement parameter set & get ops
2020-07-20 Edit minor errors
2020-07-29 Update locking functions
2020-08-06 Catchup commit.
    Hardware testing partially successful
    Interrupts not working
2020-08-06 corrected .hex addr
2020-08-06 correct hex now
2020-08-06 Update .hex file
2020-08-06 Test PWM level detection
2020-08-07 Rough main loop working
    Known bugs: uart drops chars...
2020-08-14 Update doc
2020-08-17 Testing build
2020-08-19 Update Doc with sources
2020-08-24 Test interrupts
2020-08-24 Blink interrupt test
2020-08-25 Test implementation of current measurement
2020-08-25 prod and testing files
2020-08-25 Test and Prod Build
2020-08-26 Pre-test commit
2020-08-26 Add linux makefile and test/prod build and upload script
2020-08-27 Finish Revision 1.1 layout
2020-08-27 Pre-final commit
2020-08-31 Final thesis commit
2020-09-02 Cleaning up the repo
2020-09-02 CLeaning up
2020-09-02 Finish cleaning up
    TODO: Atmel Studio Project
2020-09-02 Updated copyright notice in main.c and main.h
